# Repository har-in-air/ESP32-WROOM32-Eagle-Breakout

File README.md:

# ESP32-WROOM32-Eagle-Breakout

A breadboard compatible Eagle breakout board for Espressif's ESP32 module ESP-WROOM-32. 

## Credits
I started with the schematic and layout from 
https://github.com/StudioSophisti/ESP-WROOM-32-Eagle-Breakout
and heavily modified it for my purposes. 

## Features
Pinout on the board corresponds to the WROOM-32 module pinout. This ensures shortest path connections with minimum vias.

Adequate power planes and heatsinking for the WROOM-32 module.  

Multiple decoupling capacitors, including optional large low ESR tantalum (e.g. 330uF 6.3V). This will prevent brownout resets from current spikes when running off power supplies with limited current capacity.

Two voltage regulator options : 
1. LDO regulator - HT7833 / HT7333 in SOT89 package.  HT7833 has a higher max current and higher dropout voltage - ok for USB power. HT7333 has lower max current and lower dropout voltage - ok for Lipoly battery power if not running at max clock frequency or not using the radio.
2. Switching regulator (TPS82140) when efficiency is important and the source voltage can be up to 17V

LED on IO13. Pull-down resistor on IO2. Pull-up resistor on IO0.

No USB-UART chip on-board, to minimize deep sleep power consumption.

For testing/programming, if your USB-UART dongle 3.3V pin can provide enough power, short R3 and do not populate the regulator ICs. Otherwise, use one of the regulator options, provide power via VIN and leave R3 unpopulated.

The buttons, programming interface and regulator input pins have been placed on the edge to facilitate using the board in a case.

Pinout silkscreen on top AND bottom.

Board dimensions : ~ 36mm x 46mm

Resistors are 0603 package. Capacitors are 0603 except for C6 (tantalum C, e.g. 330uF 4V), C11 (tantalum B, can fit 220uF 4V). You can find suitable capacitors (0603 X5R, X7R) on Aliexpress and Ebay e.g. https://mcigicm.aliexpress.com/store/506373?spm=2114.10010108.0.0.15e3fdeesSP1Dd

Pcbway.com is an inexpensive pcb prototyping service I've used before : 10 PCBs  (2-layer, < 100mm x 100mm ) for US$5 + shipping. Great quality, but in my experience, it takes about 4-5 weeks from order to delivery with their cheapest shipping option.

## Assembly notes

This layout is meant for manual assembly. I have placed vias in pads for shortest path to the power planes.  The TPS82140 will have 
to be reflowed with the home-brew method of your choice - e.g. electric skillet. There's no need to risk reflowing the WROOM-32, just put thermal paste on the ground pad before hand-soldering the module pins.

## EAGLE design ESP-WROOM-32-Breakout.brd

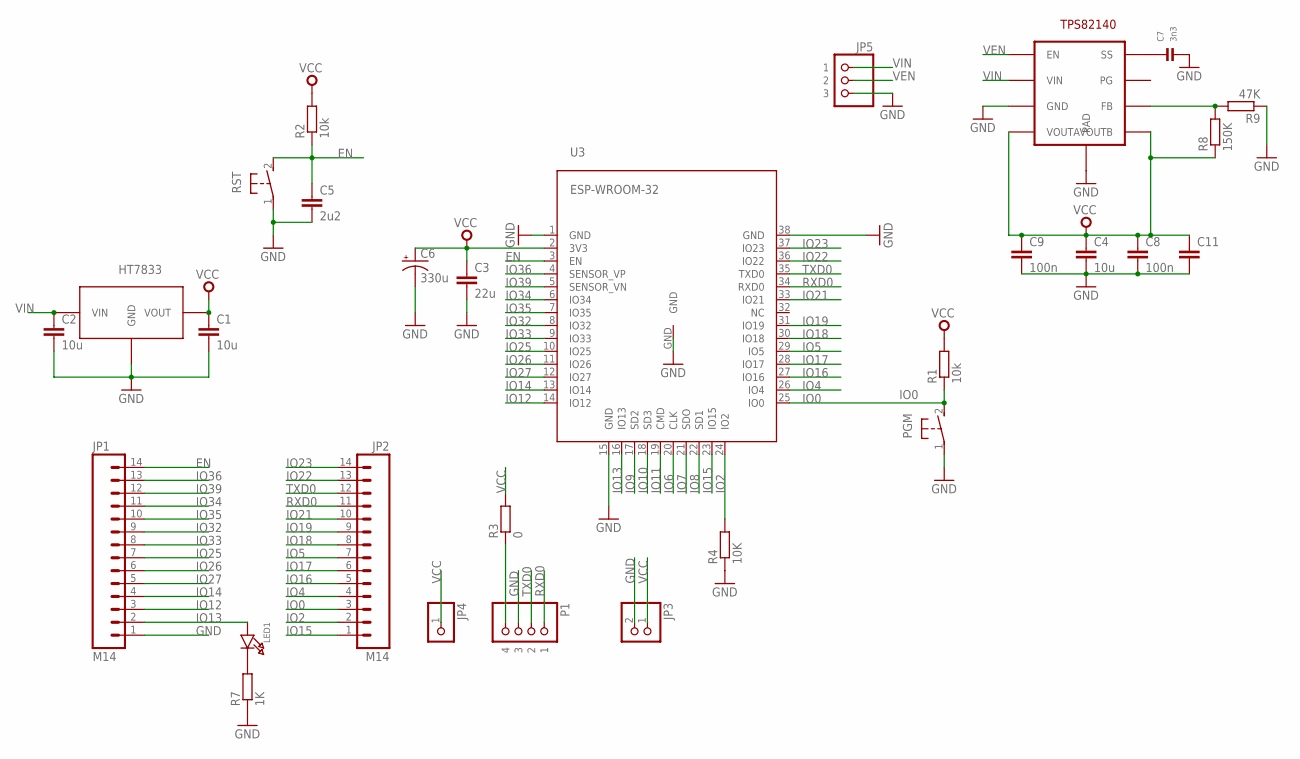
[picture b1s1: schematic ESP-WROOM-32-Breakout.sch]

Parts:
C1, C2, C4: 10u; C0603
C3: 22u; 0805
C5: 2u2; C0603
C6: 330u; VISHAY_C
C7: 3n3; 0603
C8, C9: 100n; C0603
C11: CAPSMD; GRM43D
JP1, JP2: M14; 1X14
JP3: HEADER-1X2ROUND; 1X02_ROUND
JP4: HEADER-1X1ROUND; 1X01_ROUND
JP5: HEADER-1X3ROUND; 1X03_ROUND
LED1: LED0603; CHIPLED_0603
P1: HEADER-1X4ROUND; 1X04_ROUND
PGM: DTSM-3
R1, R2: 10k; R0603
R3: 0; R0603
R4: 10K; R0603
R7: 1K; R0603
R8: 150K; R0603
R9: 47K; R0603
RST: DTSM-3
U3: ESP-WROOM-32
U$1: HT7833; SOT89
U$2: TPS82140

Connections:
EN: C5.1, JP1.14, R2.1, RST.2, U3.3 (EN)
GND: C1.2, C2.2, C3.2, C4.2, C5.2, C6.-, C7.2, C8.2, C9.2, C11.C (2), JP1.1, JP3.2, JP5.3, P1.3, PGM.1, R4.1, R7.1, R9.1, RST.1, U3.1 (GND), U3.15 (GND), U3.38 (GND), U3.GND, U$1.GND, U$2.P$3 (GND), U$2.P$9 (PAD)
IO0: JP2.3, PGM.2, R1.1, U3.25 (IO0)
IO2: JP2.2, R4.2, U3.24 (IO2)
IO4: JP2.4, U3.26 (IO4)
IO5: JP2.7, U3.29 (IO5)
IO6: U3.20 (CLK)
IO7: U3.21 (SDO)
IO8: U3.22 (SD1)
IO9: U3.17 (SD2)
IO10: U3.18 (SD3)
IO11: U3.19 (CMD)
IO12: JP1.3, U3.14 (IO12)
IO13: JP1.2, LED1.A, U3.16 (IO13)
IO14: JP1.4, U3.13 (IO14)
IO15: JP2.1, U3.23 (IO15)
IO16: JP2.5, U3.27 (IO16)
IO17: JP2.6, U3.28 (IO17)
IO18: JP2.8, U3.30 (IO18)
IO19: JP2.9, U3.31 (IO19)
IO21: JP2.10, U3.33 (IO21)
IO22: JP2.13, U3.36 (IO22)
IO23: JP2.14, U3.37 (IO23)
IO25: JP1.7, U3.10 (IO25)
IO26: JP1.6, U3.11 (IO26)
IO27: JP1.5, U3.12 (IO27)
IO32: JP1.9, U3.8 (IO32)
IO33: JP1.8, U3.9 (IO33)
IO34: JP1.11, U3.6 (IO34)
IO35: JP1.10, U3.7 (IO35)
IO36: JP1.13, U3.4 (SENSOR_VP)
IO39: JP1.12, U3.5 (SENSOR_VN)
unnamed: P1.4, R3.1
unnamed: LED1.C, R7.2
unnamed: C7.1, U$2.P$8 (SS)
unnamed: R8.2, R9.2, U$2.P$6 (FB)
RXD0: JP2.11, P1.1, U3.34 (RXD0)
TXD0: JP2.12, P1.2, U3.35 (TXD0)
VCC: C1.1, C3.1, C4.1, C6.+, C8.1, C9.1, C11.A (1), JP3.1, JP4.1, R1.2, R2.2, R3.2, R8.1, U3.2 (3V3), U$1.VOUT, U$2.P$4 (VOUTA), U$2.P$5 (VOUTB)
VEN: JP5.2, U$2.P$1 (EN)
VIN: C2.1, JP5.1, U$1.VIN, U$2.P$2 (VIN)

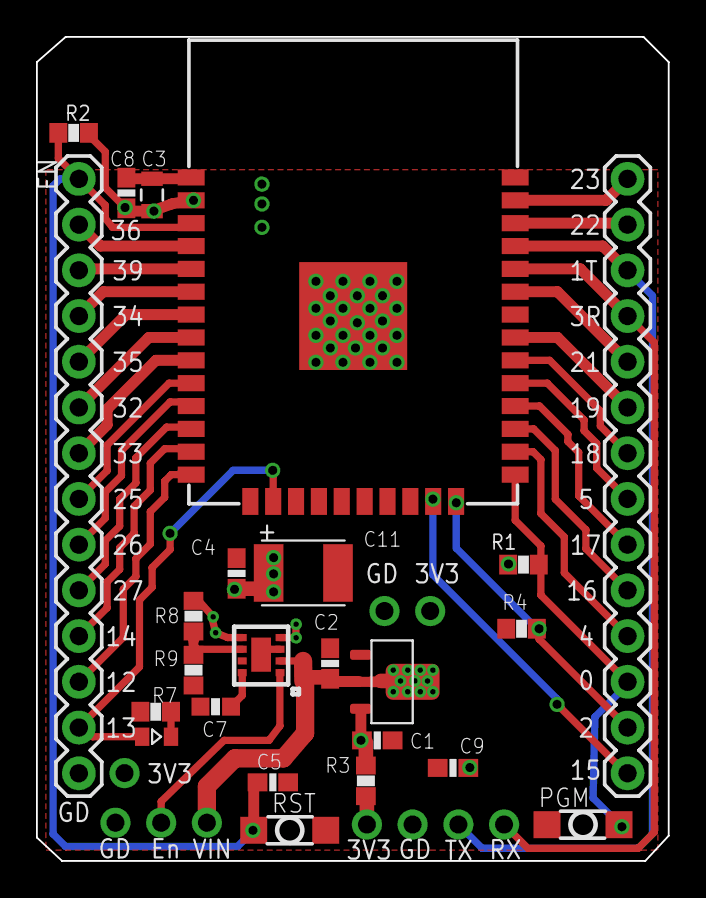
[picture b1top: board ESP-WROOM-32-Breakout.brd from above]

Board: 2 copper layers, 35.1 x 45.8 mm, 29 parts (1 on the bottom side), 35 nets.

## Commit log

2017-10-10 pinout silkscreen on bottom, wider traces
2017-11-11 Add files via upload
    moved led to pin 13, changed cap package C11 (now can accomodate tantalum B size e.g. 220uf 4V), remove thermals on some footprints for contiguous ground plane

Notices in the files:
parts and their libraries:
SparkFun-Connectors: Licensing: Creative Commons ShareAlike 4.0 International - https://creativecommons.org/licenses/by-sa/4.0
